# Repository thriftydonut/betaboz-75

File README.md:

# betaboz-75
 My second real PCB! Spaced 75% layout with 1 rotary encoder and 6/7 macro keys depending on layout.

# KLE
 http://www.keyboard-layout-editor.com/#/gists/8e6c9abece3fac9ff40674bf15e3c7ff

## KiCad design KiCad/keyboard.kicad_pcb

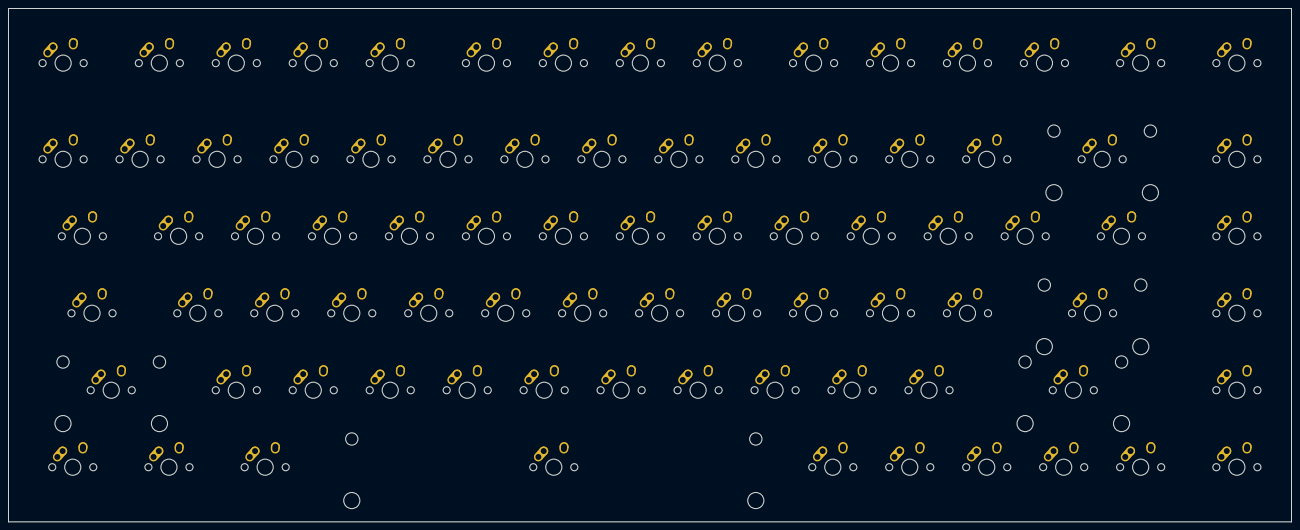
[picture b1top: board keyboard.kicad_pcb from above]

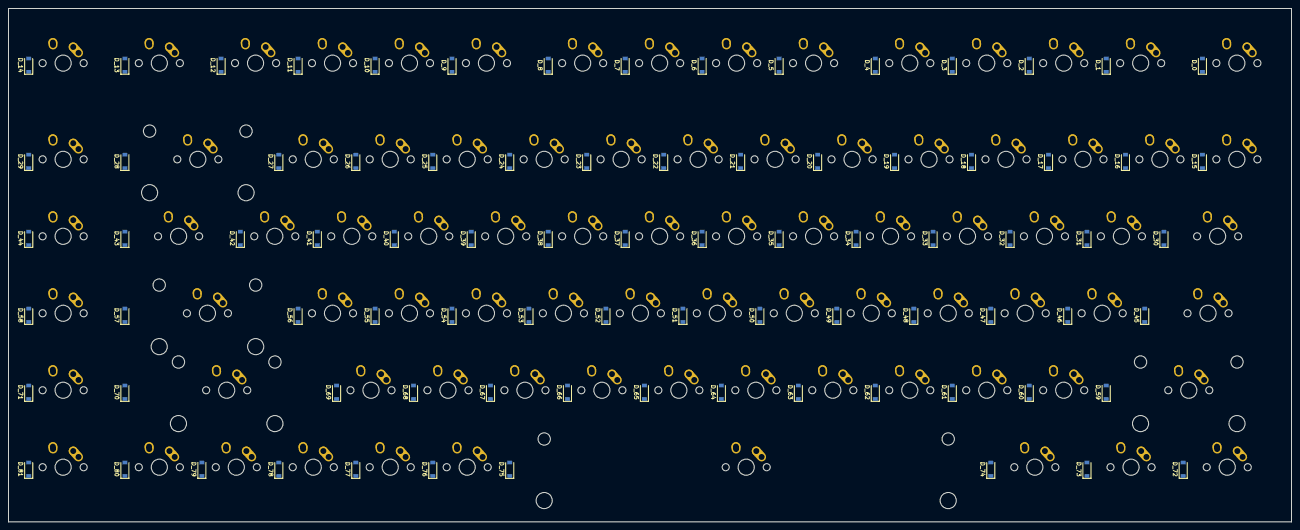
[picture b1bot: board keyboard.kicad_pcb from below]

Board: 2 copper layers, 317.6 x 127.1 mm, 164 parts (82 on the bottom side), 104 nets, no tracks yet.

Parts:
D_0, D_1, D_2, D_3, D_4, D_5, D_6, D_7, D_8, D_9, D_10, D_11, D_12, D_13, D_14, D_15, D_16, D_17, D_18, D_19, D_20, D_21, D_22, D_23, D_24, D_25, D_26, D_27, D_28, D_29, D_30, D_31, D_32, D_33, D_34, D_35, D_36, D_37, D_38, D_39, D_40, D_41, D_42, D_43, D_44, D_45, D_46, D_47, D_48, D_49, D_50, D_51, D_52, D_53, D_54, D_55, D_56, D_57, D_58, D_59, D_60, D_61, D_62, D_63, D_64, D_65, D_66, D_67, D_68, D_69, D_70, D_71, D_72, D_73, D_74, D_75, D_76, D_77, D_78, D_79, D_80, D_81: D; D_SOD-123
K_0, K_1, K_2, K_3, K_4, K_5, K_6, K_7, K_8, K_9, K_10, K_11, K_12, K_13, K_14, K_15, K_16, K_17, K_18, K_19, K_20, K_21, K_22, K_23, K_24, K_25, K_26, K_27, K_29, K_31, K_32, K_33, K_34, K_35, K_36, K_37, K_38, K_39, K_40, K_41, K_42, K_44, K_46, K_47, K_48, K_49, K_50, K_51, K_52, K_53, K_54, K_55, K_56, K_58, K_60, K_61, K_62, K_63, K_64, K_65, K_66, K_67, K_68, K_69, K_71, K_76, K_77, K_78, K_79, K_80, K_81: KEYSW; MX-1U-NoLED
K_28: KEYSW; MX-2U-NoLED
K_30, K_43: KEYSW; MX-1.5U-NoLED
K_45: KEYSW; MX-1.75U-NoLED
K_57, K_59: KEYSW; MX-2.25U-NoLED
K_70: KEYSW; MX-2.75U-NoLED
K_72, K_73, K_74: KEYSW; MX-1.25U-NoLED
K_75: KEYSW; MX-6.25U-NoLED

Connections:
unnamed: D_0.2, K_0.2
unnamed: D_1.2, K_1.2
unnamed: D_2.2, K_2.2
unnamed: D_3.2, K_3.2
unnamed: D_4.2, K_4.2
unnamed: D_5.2, K_5.2
unnamed: D_6.2, K_6.2
unnamed: D_7.2, K_7.2
unnamed: D_8.2, K_8.2
unnamed: D_9.2, K_9.2
unnamed: D_10.2, K_10.2
unnamed: D_11.2, K_11.2
unnamed: D_12.2, K_12.2
unnamed: D_13.2, K_13.2
unnamed: D_14.2, K_14.2
unnamed: D_15.2, K_15.2
unnamed: D_16.2, K_16.2
unnamed: D_17.2, K_17.2
unnamed: D_18.2, K_18.2
unnamed: D_19.2, K_19.2
unnamed: D_20.2, K_20.2
unnamed: D_21.2, K_21.2
unnamed: D_22.2, K_22.2
unnamed: D_23.2, K_23.2
unnamed: D_24.2, K_24.2
unnamed: D_25.2, K_25.2
unnamed: D_26.2, K_26.2
unnamed: D_27.2, K_27.2
unnamed: D_28.2, K_28.2
unnamed: D_29.2, K_29.2
unnamed: D_30.2, K_30.2
unnamed: D_31.2, K_31.2
unnamed: D_32.2, K_32.2
unnamed: D_33.2, K_33.2
unnamed: D_34.2, K_34.2
unnamed: D_35.2, K_35.2
unnamed: D_36.2, K_36.2
unnamed: D_37.2, K_37.2
unnamed: D_38.2, K_38.2
unnamed: D_39.2, K_39.2
unnamed: D_40.2, K_40.2
unnamed: D_41.2, K_41.2
unnamed: D_42.2, K_42.2
unnamed: D_43.2, K_43.2
unnamed: D_44.2, K_44.2
unnamed: D_45.2, K_45.2
unnamed: D_46.2, K_46.2
unnamed: D_47.2, K_47.2
unnamed: D_48.2, K_48.2
unnamed: D_49.2, K_49.2
unnamed: D_50.2, K_50.2
unnamed: D_51.2, K_51.2
unnamed: D_52.2, K_52.2
unnamed: D_53.2, K_53.2
unnamed: D_54.2, K_54.2
unnamed: D_55.2, K_55.2
unnamed: D_56.2, K_56.2
unnamed: D_57.2, K_57.2
unnamed: D_58.2, K_58.2
unnamed: D_59.2, K_59.2
unnamed: D_60.2, K_60.2
unnamed: D_61.2, K_61.2
unnamed: D_62.2, K_62.2
unnamed: D_63.2, K_63.2
unnamed: D_64.2, K_64.2
unnamed: D_65.2, K_65.2
unnamed: D_66.2, K_66.2
unnamed: D_67.2, K_67.2
unnamed: D_68.2, K_68.2
unnamed: D_69.2, K_69.2
unnamed: D_70.2, K_70.2
unnamed: D_71.2, K_71.2
unnamed: D_72.2, K_72.2
unnamed: D_73.2, K_73.2
unnamed: D_74.2, K_74.2
unnamed: D_75.2, K_75.2
unnamed: D_76.2, K_76.2
unnamed: D_77.2, K_77.2
unnamed: D_78.2, K_78.2
unnamed: D_79.2, K_79.2
unnamed: D_80.2, K_80.2
unnamed: D_81.2, K_81.2
col0: K_0.1, K_15.1, K_30.1, K_45.1, K_72.1
col1: K_1.1, K_16.1, K_59.1, K_73.1
col2: K_2.1, K_17.1, K_31.1, K_46.1, K_60.1
col3: K_3.1, K_18.1, K_32.1, K_47.1, K_61.1, K_74.1
col4: K_4.1, K_19.1, K_33.1, K_48.1, K_62.1
col5: K_20.1, K_34.1, K_49.1, K_63.1
col6: K_5.1, K_21.1, K_35.1, K_50.1, K_64.1, K_75.1
col7: K_6.1, K_22.1, K_36.1, K_51.1, K_65.1
col8: K_7.1, K_23.1, K_37.1, K_52.1, K_66.1
col9: K_8.1, K_24.1, K_38.1, K_53.1, K_67.1
col10: K_9.1, K_25.1, K_39.1, K_54.1, K_68.1, K_76.1
col11: K_10.1, K_26.1, K_40.1, K_55.1, K_69.1, K_77.1
col12: K_11.1, K_27.1, K_41.1, K_56.1, K_78.1
col13: K_12.1, K_42.1, K_57.1, K_70.1, K_79.1
col14: K_13.1, K_28.1, K_43.1, K_80.1
col15: K_14.1, K_29.1, K_44.1, K_58.1, K_71.1, K_81.1
row0: D_0.1, D_1.1, D_2.1, D_3.1, D_4.1, D_5.1, D_6.1, D_7.1, D_8.1, D_9.1, D_10.1, D_11.1, D_12.1, D_13.1, D_14.1
row1: D_15.1, D_16.1, D_17.1, D_18.1, D_19.1, D_20.1, D_21.1, D_22.1, D_23.1, D_24.1, D_25.1, D_26.1, D_27.1, D_28.1, D_29.1
row2: D_30.1, D_31.1, D_32.1, D_33.1, D_34.1, D_35.1, D_36.1, D_37.1, D_38.1, D_39.1, D_40.1, D_41.1, D_42.1, D_43.1, D_44.1
row3: D_45.1, D_46.1, D_47.1, D_48.1, D_49.1, D_50.1, D_51.1, D_52.1, D_53.1, D_54.1, D_55.1, D_56.1, D_57.1, D_58.1
row4: D_59.1, D_60.1, D_61.1, D_62.1, D_63.1, D_64.1, D_65.1, D_66.1, D_67.1, D_68.1, D_69.1, D_70.1, D_71.1
row5: D_72.1, D_73.1, D_74.1, D_75.1, D_76.1, D_77.1, D_78.1, D_79.1, D_80.1, D_81.1

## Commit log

2021-08-30 Appended layout from kb.xyz.is
2021-08-30 Added submodules
